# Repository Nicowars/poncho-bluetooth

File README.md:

# poncho-bluetooth
Repositorio para el desarrollo de un Poncho que implementa Bluetooth para la EDU-CIAA

Para poder utilizarse correctamente el proyecto, debe sobreescribirse el archivo ubicado en /modules/drivers/cortexM4/lpc43xx/lpc4337/src/ciaaDriverDio.c del Firmware de la CIAA por el que esta incluido en projects/Firmware. Luego debe recompilarse el Firmware.

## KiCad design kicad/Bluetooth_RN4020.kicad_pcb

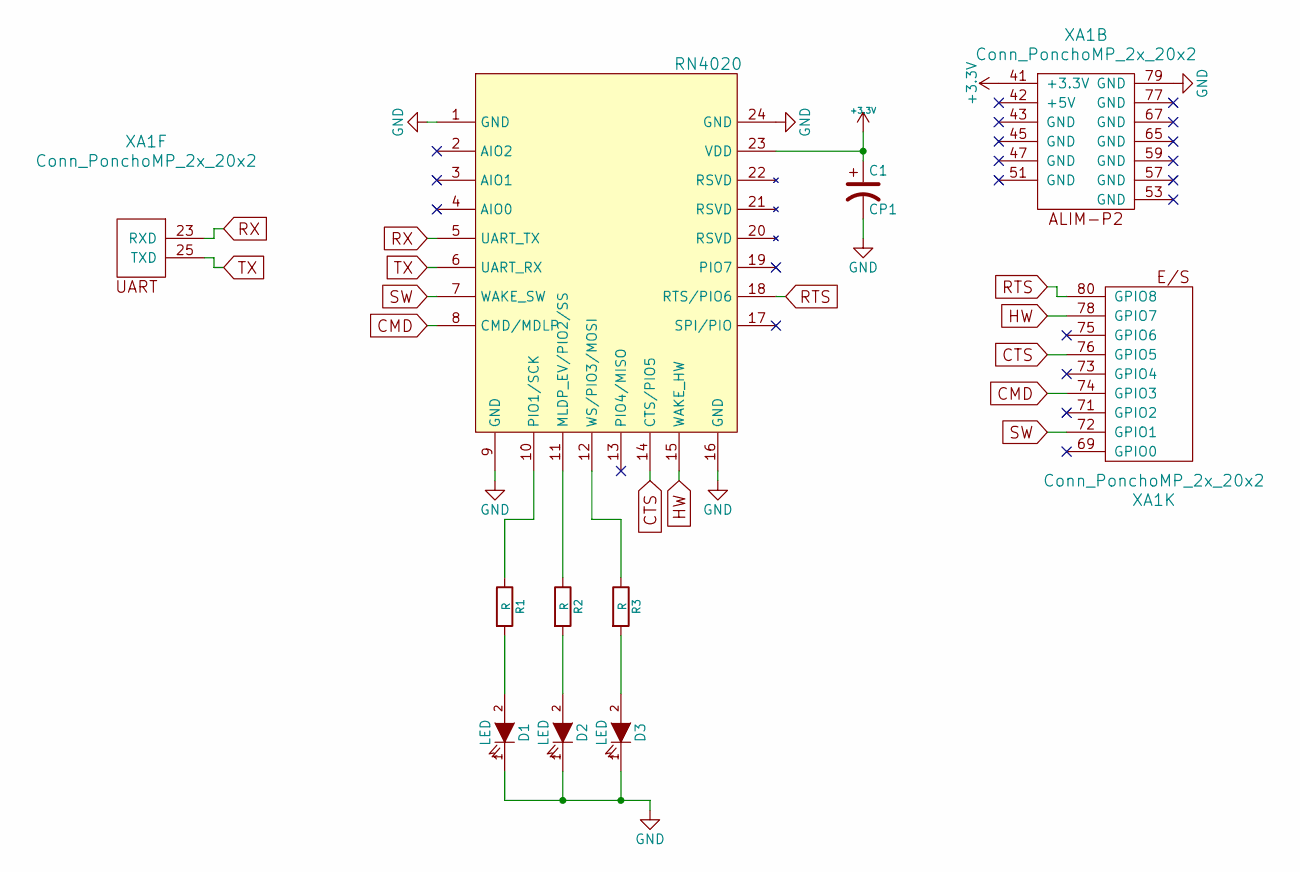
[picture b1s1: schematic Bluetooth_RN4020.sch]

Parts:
C1: CP1; TantalC_SizeB_EIA-3528_Reflow
D1, D2, D3: LED; LED-3MM
R1, R2, R3: R; R_1206
U1: RN4020
XA1: Conn_PonchoMP_2x_20x2

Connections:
+3V3: C1.1, U1.23 (VDD), XA1.41 (+3.3V)
CMD: U1.8 (CMD/MDLP), XA1.74 (GPIO3)
CTS: U1.14 (CTS/PIO5), XA1.76 (GPIO5)
GND: C1.2, D1.1 (K), D2.1 (K), D3.1 (K), U1.1 (GND), U1.9 (GND), U1.16 (GND), U1.24 (GND), XA1.79 (GND)
HW: U1.15 (WAKE_HW), XA1.78 (GPIO7)
unnamed: D1.2 (A), R1.2
unnamed: D2.2 (A), R2.2
unnamed: D3.2 (A), R3.2
unnamed: R1.1, U1.10 (PIO1/SCK)
unnamed: R2.1, U1.11 (MLDP_EV/PIO2/SS)
unnamed: R3.1, U1.12 (WS/PIO3/MOSI)
RTS: U1.18 (RTS/PIO6), XA1.80 (GPIO8)
RX: U1.5 (UART_TX), XA1.23 (RXD)
SW: U1.7 (WAKE_SW), XA1.72 (GPIO1)
TX: U1.6 (UART_RX), XA1.25 (TXD)

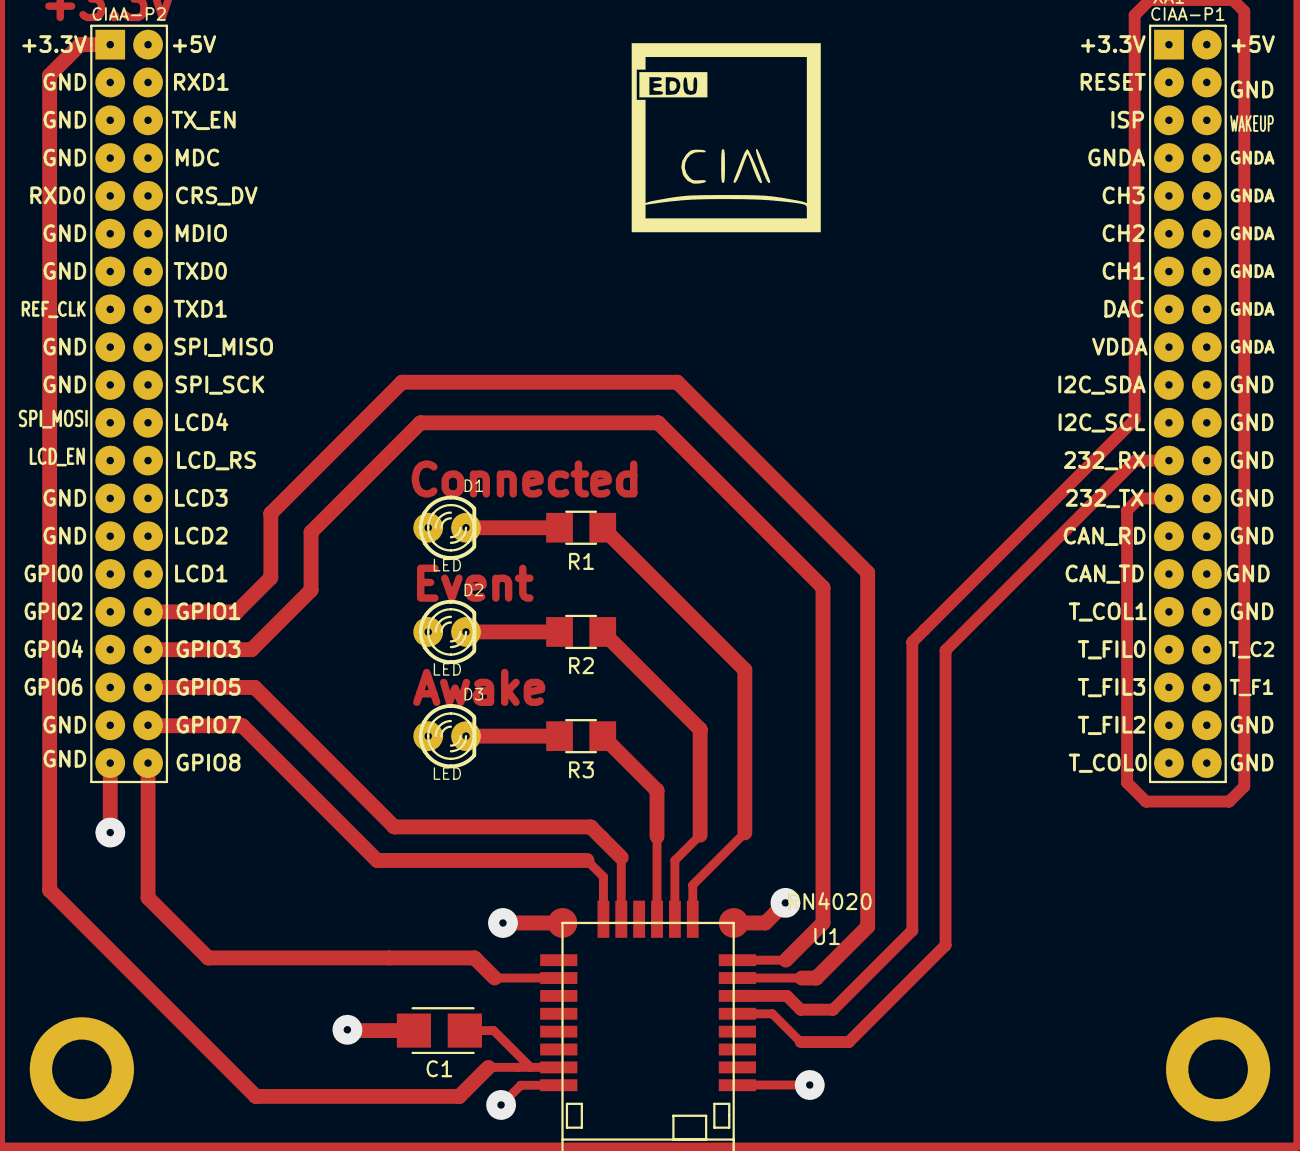
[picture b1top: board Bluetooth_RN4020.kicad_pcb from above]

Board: 2 copper layers, 9 parts (0 on the bottom side), 15 nets.

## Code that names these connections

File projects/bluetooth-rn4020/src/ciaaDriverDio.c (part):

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   Chip_SCU_PinMux(4,1,MD_PUP|MD_EZI|MD_ZI,FUNC0); /* GPIO2[1]  */
   Chip_SCU_PinMux(4,2,MD_PUP|MD_EZI|MD_ZI,FUNC0); /* GPIO2[2]  */
   Chip_SCU_PinMux(4,3,MD_PUP|MD_EZI|MD_ZI,FUNC0); /* GPIO2[3]  */
   Chip_SCU_PinMux(7,3,MD_PUP|MD_EZI|MD_ZI,FUNC0); /* GPIO3[11] */
   Chip_SCU_PinMux(7,4,MD_PUP|MD_EZI|MD_ZI,FUNC0); /* GPIO3[12] */
   Chip_SCU_PinMux(7,5,MD_PUP|MD_EZI|MD_ZI,FUNC0); /* GPIO3[13] */
   Chip_SCU_PinMux(7,6,MD_PUP|MD_EZI|MD_ZI,FUNC0); /* GPIO3[14] */

   Chip_GPIO_SetDir(LPC_GPIO_PORT, 2,0xF, 0);
   Chip_GPIO_SetDir(LPC_GPIO_PORT, 3, 0xF<<11, 0);

   /* MOSFETs */
   Chip_SCU_PinMux(4,8,MD_PUP|MD_EZI,FUNC4);  /* GPIO5[12] */
   Chip_SCU_PinMux(4,9,MD_PUP|MD_EZI,FUNC4);  /* GPIO5[13] */
   Chip_SCU_PinMux(4,10,MD_PUP|MD_EZI,FUNC4); /* GPIO5[14] */
   Chip_SCU_PinMux(1,5,MD_PUP|MD_EZI,FUNC0);  /* GPIO1[8]  */
   Chip_GPIO_SetDir(LPC_GPIO_PORT, 5,(1<<12)|(1<<13)|(1<<14),1);
   Chip_GPIO_SetDir(LPC_GPIO_PORT, 1,(1<<8),1);
   Chip_GPIO_ClearValue(LPC_GPIO_PORT, 5,(1<<12)|(1<<13)|(1<<14));
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   Chip_SCU_PinMux(4,4,MD_PUP|MD_EZI,FUNC0); /* GPIO2[4] */
   Chip_SCU_PinMux(4,5,MD_PUP|MD_EZI,FUNC0); /* GPIO2[5] */
   Chip_SCU_PinMux(4,6,MD_PUP|MD_EZI,FUNC0); /* GPIO2[6] */
   Chip_SCU_PinMux(2,1,MD_PUP|MD_EZI,FUNC4); /* GPIO5[1] */
   Chip_GPIO_SetDir(LPC_GPIO_PORT, 2,(1<<4)|(1<<5)|(1<<6),1);
   Chip_GPIO_SetDir(LPC_GPIO_PORT, 5,(1<<1),1);
   Chip_GPIO_ClearValue(LPC_GPIO_PORT, 2,(1<<4)|(1<<5)|(1<<6));
   Chip_GPIO_ClearValue(LPC_GPIO_PORT, 5,(1<<1));

   /* LV-TTL GPIOs (not used yet) */
   Chip_SCU_PinMux(6,1,MD_PUP|MD_EZI|MD_ZI,FUNC0); /* GPIO0/P6_1/GPIO3[0] */
   Chip_SCU_PinMux(2,5,MD_PUP|MD_EZI|MD_ZI,FUNC4); /* GPIO1/P2_5/GPIO5[5] */
#elif (BOARD == edu_ciaa_nxp)
   /* Switches */
   Chip_SCU_PinMux(1,0,MD_PUP|MD_EZI|MD_ZI,FUNC0); /* GPIO0[4], SW1 */
   Chip_SCU_PinMux(1,1,MD_PUP|MD_EZI|MD_ZI,FUNC0); /* GPIO0[8], SW2 */
   Chip_SCU_PinMux(1,2,MD_PUP|MD_EZI|MD_ZI,FUNC0); /* GPIO0[9], SW3 */
   Chip_SCU_PinMux(1,6,MD_PUP|MD_EZI|MD_ZI,FUNC0); /* GPIO1[9], SW4 */

   /* PONCHO: gpIo */
   Chip_SCU_PinMux(6,12,MD_PDN|MD_EZI|MD_ZI,FUNC0); /* GPIO2[8], GPIO8 = CTS */

   Chip_GPIO_SetDir(LPC_GPIO_PORT, 0,(1<<4)|(1<<8)|(1<<9),0);
   Chip_GPIO_SetDir(LPC_GPIO_PORT, 1,(1<<9),0);
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   Chip_GPIO_SetDir(LPC_GPIO_PORT, 2,(1<<8),0);

   /* LEDs */
   Chip_SCU_PinMux(2,0,MD_PUP|MD_EZI,FUNC4);  /* GPIO5[0], LED0R */
   Chip_SCU_PinMux(2,1,MD_PUP|MD_EZI,FUNC4);  /* GPIO5[1], LED0G */
   Chip_SCU_PinMux(2,2,MD_PUP|MD_EZI,FUNC4);  /* GPIO5[2], LED0B */
   Chip_SCU_PinMux(2,10,MD_PUP|MD_EZI,FUNC0); /* GPIO0[14], LED1 */
   Chip_SCU_PinMux(2,11,MD_PUP|MD_EZI,FUNC0); /* GPIO1[11], LED2 */
   Chip_SCU_PinMux(2,12,MD_PUP|MD_EZI,FUNC0); /* GPIO1[12], LED3 */

   Chip_GPIO_SetDir(LPC_GPIO_PORT, 5,(1<<0)|(1<<1)|(1<<2),1);
   Chip_GPIO_SetDir(LPC_GPIO_PORT, 0,(1<<14),1);
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   Chip_GPIO_ClearValue(LPC_GPIO_PORT, 1,(1<<11)|(1<<12));

   /* PONCHO: gpiO */
   Chip_SCU_PinMux(6,4,MD_PUP|MD_EZI,FUNC0);	/* GPIO3[3], GPIO1 = WAKE_SW */
   Chip_SCU_PinMux(6,9,MD_PUP|MD_EZI,FUNC0);	/* GPIO3[5], GPIO5 = RTS */
   Chip_SCU_PinMux(6,11,MD_PUP|MD_EZI,FUNC0);	/* GPIO3[7], GPIO7 = WAKE_HW */
   Chip_SCU_PinMux(6,7,MD_PUP|MD_EZI,FUNC4);	/* GPIO5[15], GPIO3 = CMD */

   Chip_GPIO_SetDir(LPC_GPIO_PORT, 3,(1<<3)|(1<<5)|(1<<7),1);
   Chip_GPIO_SetDir(LPC_GPIO_PORT, 5,(1<<15),1);
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
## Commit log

2015-10-05 Datasheets
2015-10-05 Presentacion
2015-10-19 Reestructura directorios (sin proyecto kicad)
2015-10-19 Fix +directorios
2015-10-22 Primera footprint
2015-10-23 backup pen
2015-10-31 Limpieza
2015-11-01 FUSION
2015-11-02 Poncho Mediano
2015-11-02 Footprints
2015-11-02 Footprint RN4020
2015-11-02 50% Poncho
2015-11-09 New Poncho
2015-11-09 PCB Completa
2015-11-15 Casi listo
2015-11-17 Ploteo
2015-11-19 Pad Leds
2016-02-07 Proyecto
2016-02-07 RN4020.h + POSIX
2016-02-08 GPIO DIR
2016-02-15 Blinking Echo
2016-02-15 Echo RS232
2016-02-16 Last try
2016-02-17 Not-sure-if-stable Cleanup
2016-02-18 Stable <- Checked
    Un poco de limpieza y de mejora a los comentarios.
2016-02-18 Using GPIOs with POSIX
    Cuando consigamos una configuracion que ande...
    Cleanup de en serio xD
2016-02-18 New header
    Cuando estemos seguro de que todo POSIX anda...
    Dejamos los archivos_DIOasPOSIX como definitivos
2016-02-19 Cleanup. Added more LEDs.
2016-02-19 tareas pulsadores polling
2016-02-20 Footprint acondicionandose
2016-02-20 Kicad Fix
    Fix the Kicad
2016-02-20 limpieza de codigo
2016-02-20 Deleting blinking_echo. Added something.
2016-02-20 parche
2016-02-20 Reorganizacion
2016-02-20 Cambiar ubicacion README
2016-02-20 Error de tipeo
2016-02-20 Iniciañdo
2016-02-20 Reordenando codigo
2016-02-20 Modularizando
2016-02-20 Added features to RN4020 header
2016-02-20 Using HEADER-MK2. (hopefully will work)
2016-02-20 Jaime was here fixing issues
2016-02-20 Nombre TASK
2016-02-20 xtoa8. Untested.
2016-02-21 xto18. Fix1
2016-02-21 Revert "xto18. Fix1"
    This reverts commit dbc30a1bce1aaf387efd1c8ba1701ec3e7147f4f.
2016-02-21 Revert "xtoa8. Untested."
    This reverts commit 4b30420bb6128e25abb3a8a6a892bd2772da7d83.
2016-02-21 Revert "Nombre TASK"
    This reverts commit cbe7e4abbd0df764d3527fef311c0dc05d90ac37.
2016-02-21 Revert "Jaime was here fixing issues"
    This reverts commit b2956c1b9d9feeac712582e668425a70073c5619.
2016-02-21 Revert "Using HEADER-MK2. (hopefully will work)"
    This reverts commit 9fa9ac7b7040349473408e8b42816d540d1fc3b2.
2016-02-21 Revert "Revert "Using HEADER-MK2. (hopefully will work)""
    This reverts commit 16b3b15d7d406d38b6dea693941feadd3e67cc50.
2016-02-21 Revert "Revert "Jaime was here fixing issues""
    This reverts commit b4e396c0dba5dbc416c620b5a40368b85dc9dbd5.
2016-02-21 Revert "Revert "xtoa8. Untested.""
    This reverts commit 957a1962c80c74f2c578f37da13fc5a940c7073c.
2016-02-21 Revert "Revert "xto18. Fix1""
    This reverts commit 43435aa63cad0025363222c446debc3481fc0273.
2016-02-21 Revert "Revert "Revert "xto18. Fix1"""
    This reverts commit 75955d8e49eb79a8957352ffa191ceb1c78391b6.
2016-02-21 Revert "Revert "Revert "xtoa8. Untested."""
    This reverts commit 6411236e90ae7b95fa09032d08748df4bc0d5537.
2016-02-21 Revert "Revert "Revert "Jaime was here fixing issues"""
    This reverts commit 679956b0d82bb61afe1a5013e9482ba39d32765a.
2016-02-21 Revert "Revert "Revert "Using HEADER-MK2. (hopefully will work)"""
    This reverts commit 05bf12efe6998f2855171859b334fe12807c4bda.
2016-02-21 Nombre TASK agarin
2016-02-21 Renombre y limpieza
2016-02-21 comentarios
2016-02-21 Mas comentarios.
    +minor fix
2016-02-22 some +
2016-02-22 comandos 2.0
2016-04-15 Added Android Project
    Can switch state of LED1, LED2 and LED3
2016-04-16 Added LED0 Commands
    Hay que acomodar el repo para que ignore los archivos locales para
    buildear... Arma lio sino.

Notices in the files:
projects/bluetooth-rn4020/src/ciaaDriverDio.c:
Copyright 2014, 2015 Pablo Ridolfi (UTN-FRBA)
All rights reserved.
